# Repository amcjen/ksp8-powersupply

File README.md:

# ksp8-powersupply
A replacement power supply PCB for the Kurzweil KSP8

Really simple drop-in replacement for the ancient power supply that comes with the KSP8. Included are the v9.0 compatible Eagle
.sch and .brd files, as well as the raw gerbers. The zip file has all the gerbers compressed, and you can usually upload the zip
file directly to most board houses for manufacture.

If you start hearing whining from the power supply transformer, or your unit begins resetting randomly, then it's probably the
power supply, and it's probably time to replace it.

Luckily the great people at Traco make super simple drop-in power supply modules. This board simply adds the right layout, the
proper fuses, and mimic's the power-good circuit that the KSP8 expects to see (though in reality it's likely not even necessary).

The new power supply input specs are super wide, so should be usable pretty much anywhere in the world:

Voltage input:
*90-240V VAC, 47-440 Hz*

Do of course be extremely careful with the mains power coming into this! There are several exposed leads and test points.

Regardless, most of the instructions are on the back of the board, on the silkscreen. It's reproduced here for reference:

### Jumpers
- JP1 - Tie mains gnd to 5V DC gnd (default: connected)
- JP2 - Tie /pwr_ok to voltage supervisor output (default: connected)
- JP3 - Tie /pwr_ok to 5V DC gnd (default: disconnected)

### To run with the power supervisor (default)
- Place U3 and R1
- Leave JP2 uncut
- Leave JP3 open

### To run without the power supervisor
- Exclude U3 and R1
- Cut JP2
- Solder JP3

### Required Components
- U1 - Traco TML-40105 - 5V/8A output
- U2 - Traco TML-40215 - +15V/1.3A / -15V/1.3A
- U3 - Microchip MIC810LUY power supervisor
- F1/F2 - Littelfuse 05200101Z - 1.6A slow blow 5x20mm 250V fuses
- R1 - 100k 1206 resistor

You can buy Tracos at several retailers, like Mouser and Digikey. Yes, they're pricey, but they are also medical grade, have
excellent electrical specs and clean power, and have something like a 70 year mean time between failure (MTBF). So these should
definitely outlast the device (or at least the LCD!)

One last wonderful side benefit is that these supplies seem to run pretty cool, so no need to have that loud fan running anymore.
Feel free to unplug it from the front board for a more silent studio environment.

✨ Happy music making! ✨

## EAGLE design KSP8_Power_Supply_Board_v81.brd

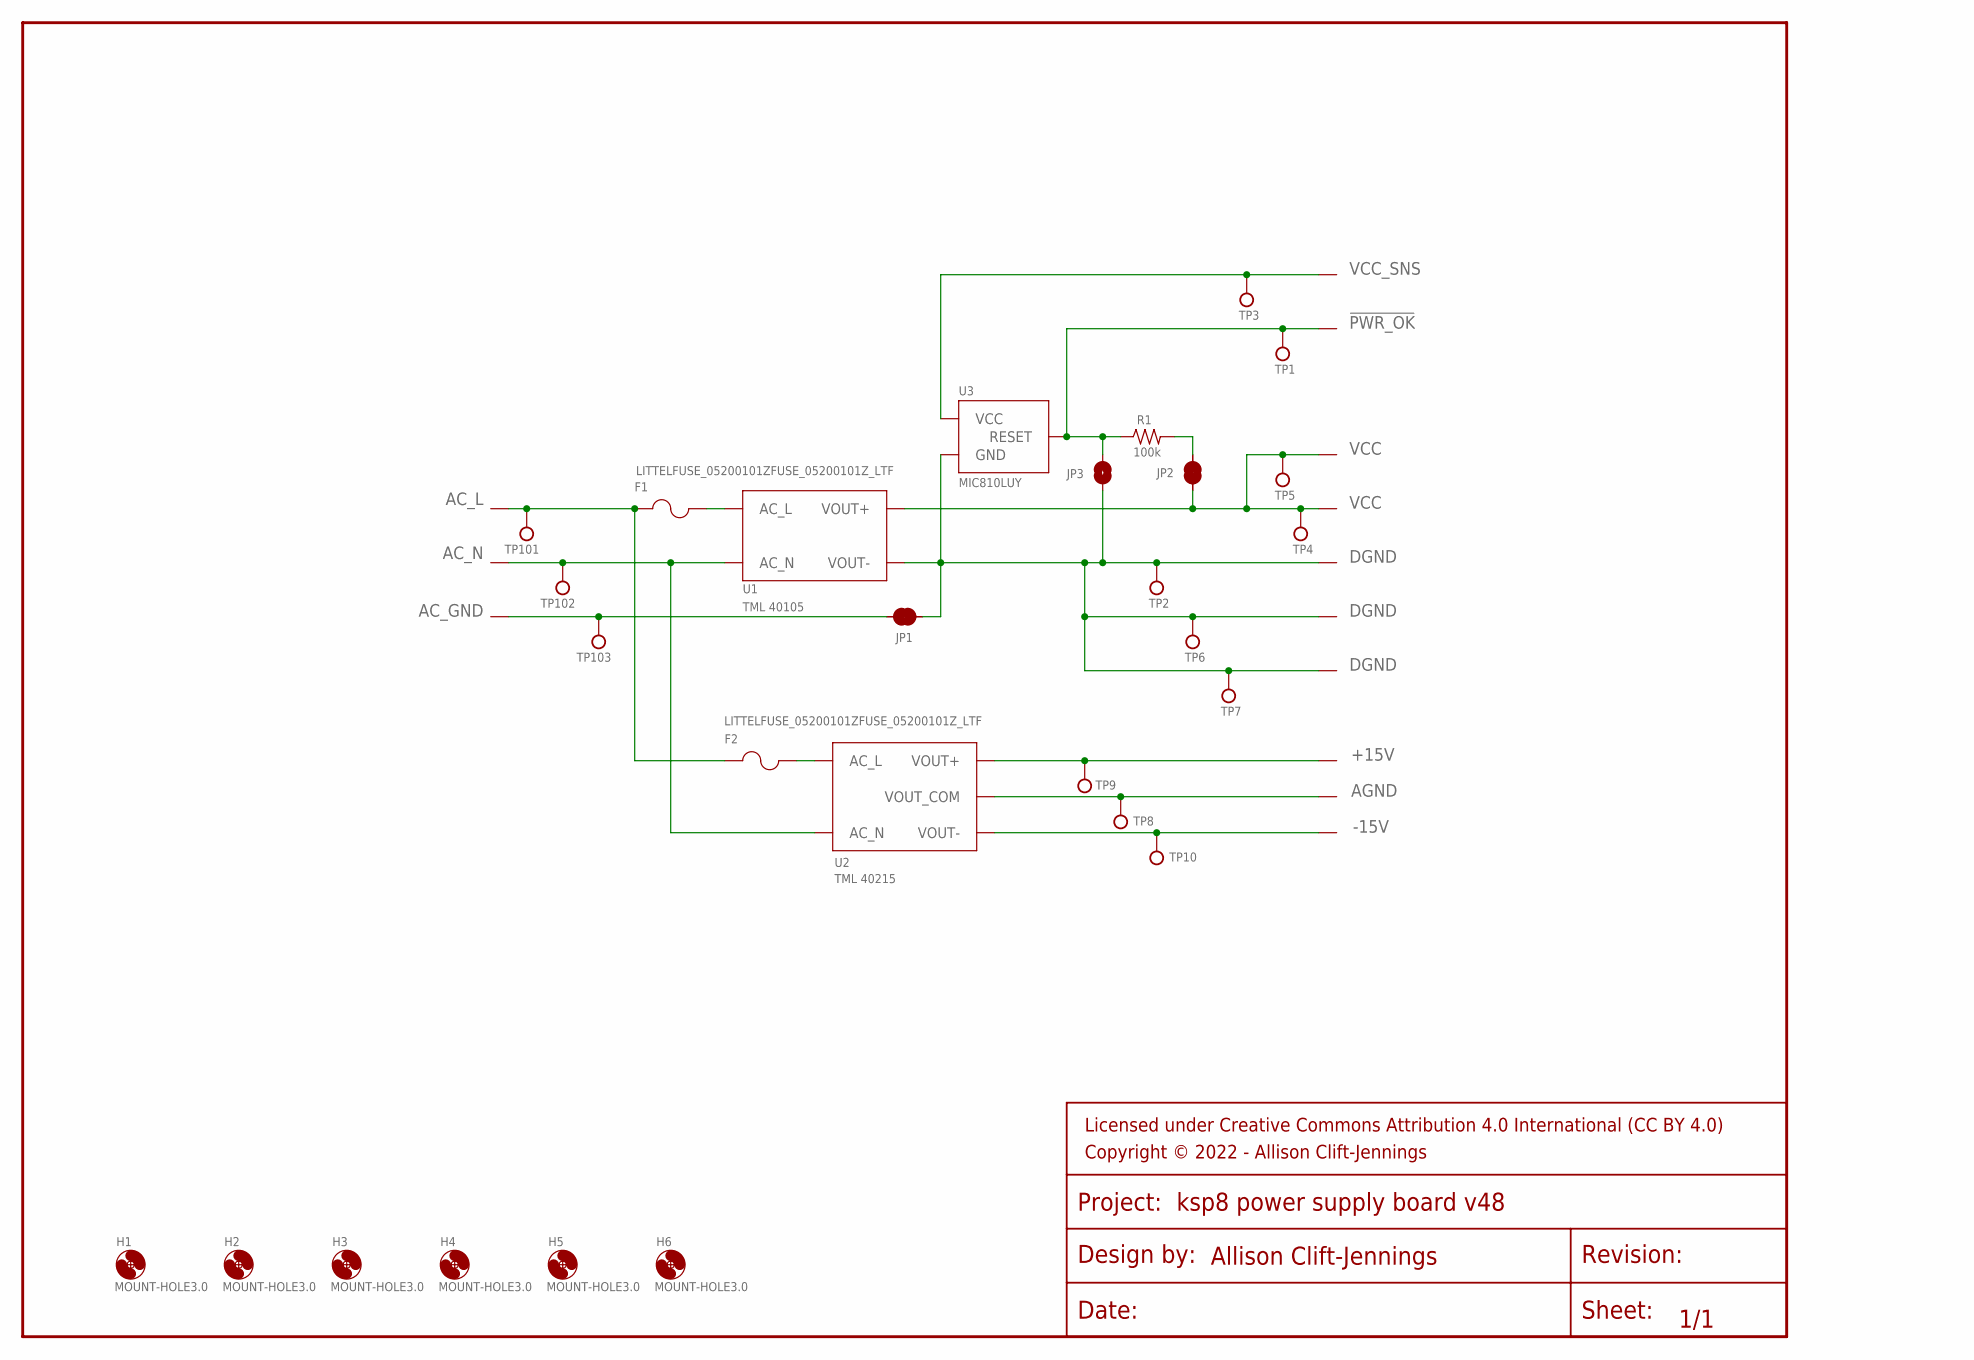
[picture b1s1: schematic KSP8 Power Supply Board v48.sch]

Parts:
AGND: PADPAD-070-LOOP; PAD-067-LOOP
F1, F2: LITTELFUSE_05200101ZFUSE_05200101Z_LTF; LITTELFUSE_05200101Z_LTF
FRAME1: FRAME-LETTER-OS; CREATIVE_COMMONS
H1, H2, H3, H4, H5, H6: MOUNT-HOLE3.0; 3,0
JP1: JUMPER-SMT_2_NO_SILK; SMT-JUMPER_2_NC_TRACE_SILK_HC
JP2: JUMPER-SMT_2_NC_TRACE_SILK; SMT-JUMPER_2_NC_TRACE_SILK
JP3: JUMPER-SMT_2_NO_SILK; SMT-JUMPER_2_NO_SILK
R1: 100k; 1206
TP1, TP2, TP3, TP4, TP5, TP6, TP7, TP8, TP9, TP10, TP101, TP102, TP103: TESTPOINT; PAD-100-RND
U1: TML 40105; TRACO_TML
U2: TML 40215; TRACO_TML
U3: MIC810LUY; SOT23
U$4, U$5, U$6, U$7, U$8, U$9, U$10, U$11, U$12, U$13, U$14, U$15: PADPAD-070-LOOP; PAD-067-LOOP

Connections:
!PWR_OK: JP3.2, R1.1, TP1.P$1, U3.2 (RESET), U$8.P$1
+15V: TP9.P$1, U2.P$4 (VOUT+), U$6.P$1
-15V: TP10.P$1, U2.P$8 (VOUT-), U$7.P$1
AC_GND: JP1.1, TP103.P$1, U$11.P$1
AC_L: F1.1, F2.1, TP101.P$1, U$4.P$1
AC_N: TP102.P$1, U1.P$3 (AC_N), U2.P$3 (AC_N), U$5.P$1
AGND: AGND.P$1, TP8.P$1, U2.P$6 (VOUT_COM)
DGND: JP1.2, JP3.1, TP2.P$1, TP6.P$1, TP7.P$1, U1.P$6 (VOUT-), U3.1 (GND), U$10.P$1, U$13.P$1, U$14.P$1
unnamed: F1.2, U1.P$2 (AC_L)
unnamed: F2.2, U2.P$2 (AC_L)
unnamed: JP2.1, R1.2
VCC: JP2.2, TP4.P$1, TP5.P$1, U1.P$4 (VOUT+), U$9.P$1, U$15.P$1
VCC_SNS: TP3.P$1, U3.3 (VCC), U$12.P$1

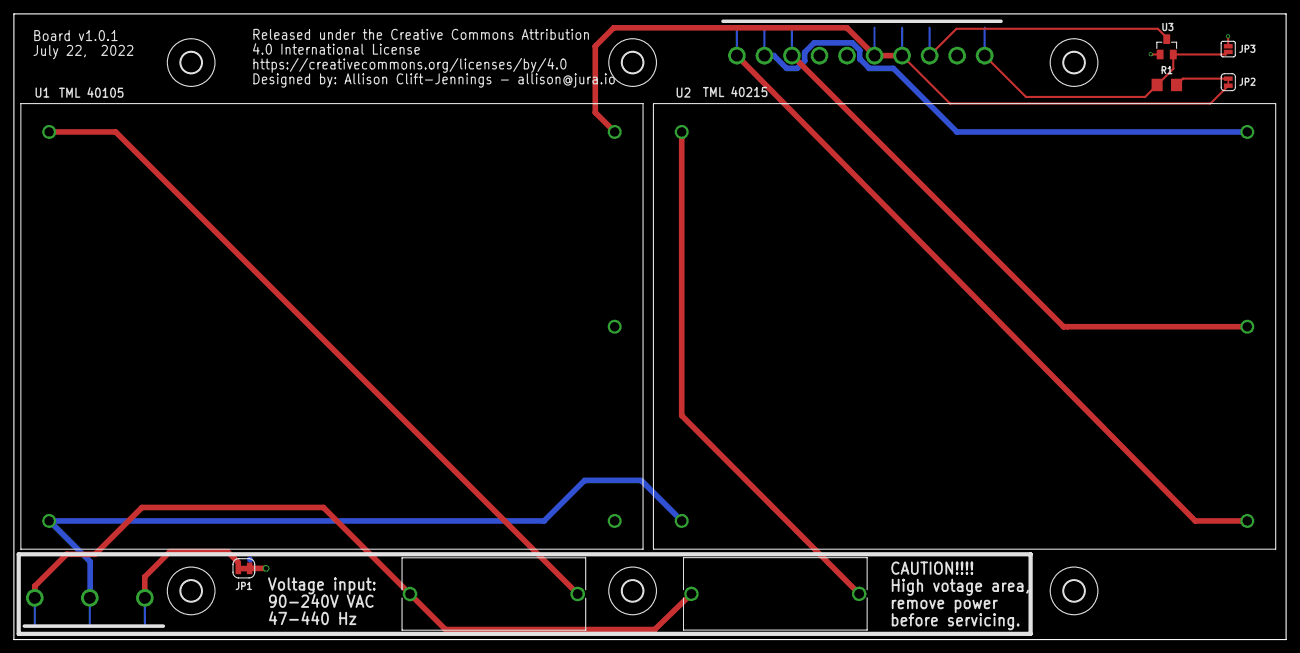
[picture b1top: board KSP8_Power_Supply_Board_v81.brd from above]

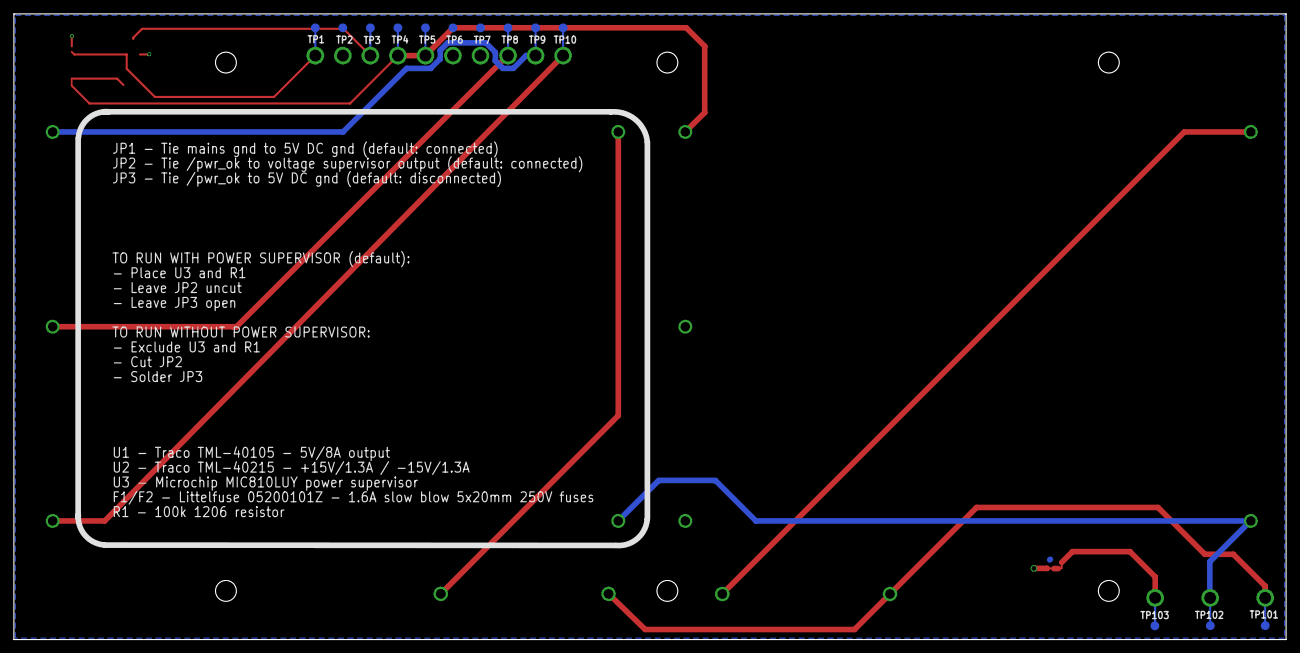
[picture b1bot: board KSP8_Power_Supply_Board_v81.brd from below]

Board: 2 copper layers, 183.0 x 90.0 mm, 42 parts (13 on the bottom side), 13 nets.

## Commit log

2022-09-05 Update README.md
    Updated readme formatting a bit

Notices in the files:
KSP8_Power_Supply_Board_v81.brd:
Released under the Creative Commons Attribution
https://creativecommons.org/licenses/by/4.0
parts and their libraries:
Tonic Library: Released under the Creative Commons Attribution 4.0 International License
Tonic Library: Licensed under Creative Commons Attribution 4.0 International (CC BY 4.0)
Tonic Library: Copyright © 2022 - Allison Clift-Jennings
